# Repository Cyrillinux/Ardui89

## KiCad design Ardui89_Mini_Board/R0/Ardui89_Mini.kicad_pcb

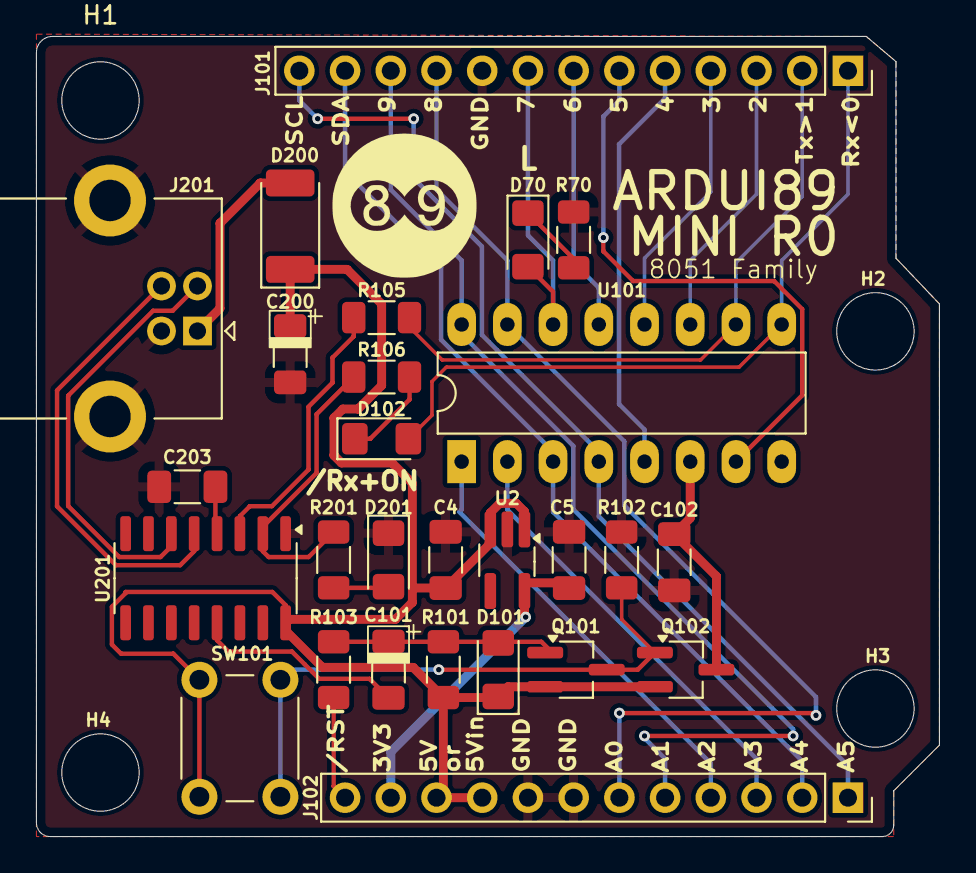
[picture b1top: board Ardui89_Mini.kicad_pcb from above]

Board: 2 copper layers, 50.2 x 44.5 mm, 31 parts (0 on the bottom side), 31 nets.

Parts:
C4, C5, C102, C203: 100n; C_1206_3216Metric_Pad1.33x1.80mm_HandSolder
C101, C200: 10µ; C_1206_POL_3216Metric_Pad1.33x1.80mm_HandSolder
D70: LED BUILTIN; D_1206_3216Metric_Pad1.42x1.75mm_HandSolder
D101, D102: 1N5819W; D_1206_3216Metric_Pad1.42x1.75mm_HandSolder
D200: SM34; D_MELF
D201: /Rx LED + OK; D_1206_3216Metric_Pad1.42x1.75mm_HandSolder
H1, H2, H3: MountingHole; MountingHole_4.3mm_M4_DIN965
H4: Mounting Hole 4.3mm; MountingHole_4.3mm_M4_DIN965
J101: Conn_01x13; PinSocket_1x13_P2.54mm_Vertical
J102: Conn_01x12; PinSocket_1x12_P2.54mm_Vertical
J201: USB_TYPE_B; USB_B_Lumberg_2411_02_Horizontal
Q101, Q102: MMBT2907; TSOT-23_HandSoldering
R70, R101, R103, R201: 1k; R_1206_3216Metric_Pad1.30x1.75mm_HandSolder
R102: 4k7; R_1206_3216Metric_Pad1.30x1.75mm_HandSolder
R105, R106: 330; R_1206_3216Metric_Pad1.30x1.75mm_HandSolder
SW101: SW_Push; SW_PUSH_6mm
U2: LP2985-33DBVR; TSOT-23-5_HandSoldering
U101: DIP-16_W7.62mm_LongPads
U201: CH340C; SOIC-16_3.9x9.9mm_P1.27mm

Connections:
/3.3V: C5.1, J102.11, U2.5 (VOUT)
/A0_D8: J101.10, J102.6, U101.15 ((CCP1/ADC0)_P1.0)
/A1_D9: J101.11, J102.5, U101.16 ((CCP0/ADC1)_P1.1)
/A2: J102.4, U101.1 ((CMP0/ECI/SS/ADC2)_P1.2)
/A3: J102.3, U101.2 ((MOSI/ADC3)_P1.3)
/A4_SDA: J101.12, J102.2, U101.3 ((MISO/ADC4)_P1.4)
/A5_SCL: J101.13, J102.1, U101.4 ((SCLK/ADC5)_P1.5)
/D0: D102.2 (A), J101.1, U101.9 ((RxD/_INT4)_P3.0)
/D1: J101.2, R105.1, U101.10 ((TxD/T2)_P3.1)
/D2: J101.3, U101.11 ((INT0)_P3.2)
/D3: J101.4, U101.12 ((INT1)_P3.3)
/D4: J101.5, U101.5 ((RESET/CMP-/SyCK0)_P5.4)
/D5: J101.6, U101.7 ((CMP+)_P5.5)
/D6: J101.7, U101.13 ((RxD2/_INT2/CCP12)_P3.6)
/D7: D70.2 (A), J101.8, U101.14 ((TxD2/_INT3/CCP22)_P3.7)
/D+: J201.3 (D+), U201.5 (UD+)
/D-: J201.2 (D-), U201.6 (UD-)
/RTS: C101.2, U201.13 (~DTR)
/Rx: R106.2, R201.1, U201.2 (TXD)
/Tx: R105.2, U201.3 (RXD)
//RST: J102.12, R103.2
GND: C4.2, C5.2, C102.2, C200.2, C203.2, D201.1 (K), J101.9, J102.7, J102.8, J201.4 (GND), J201.5 (Shield_1), R70.2, R102.2, U2.2 (GND), U201.1 (GND)
unnamed: D70.1 (K), R70.1
unnamed: C101.1, D101.2 (A), Q101.1 (B), R101.2, R103.1
unnamed: D102.1 (K), R106.1
unnamed: D200.2 (A), J201.1 (Vbus)
unnamed: D201.2 (A), R201.2
unnamed: Q101.3 (C), Q102.1 (B), R102.1, SW101.1
unnamed: C102.1, Q102.3 (C), U101.6 (VCC)
unnamed: C203.1, U201.4 (V3)
VCC: C4.1, C200.1, D101.1 (K), D200.1 (K), J102.9, J102.10, Q101.2 (E), Q102.2 (E), R101.1, SW101.2, U2.1 (VIN), U2.3 (ON/~OFF), U201.16 (VCC)

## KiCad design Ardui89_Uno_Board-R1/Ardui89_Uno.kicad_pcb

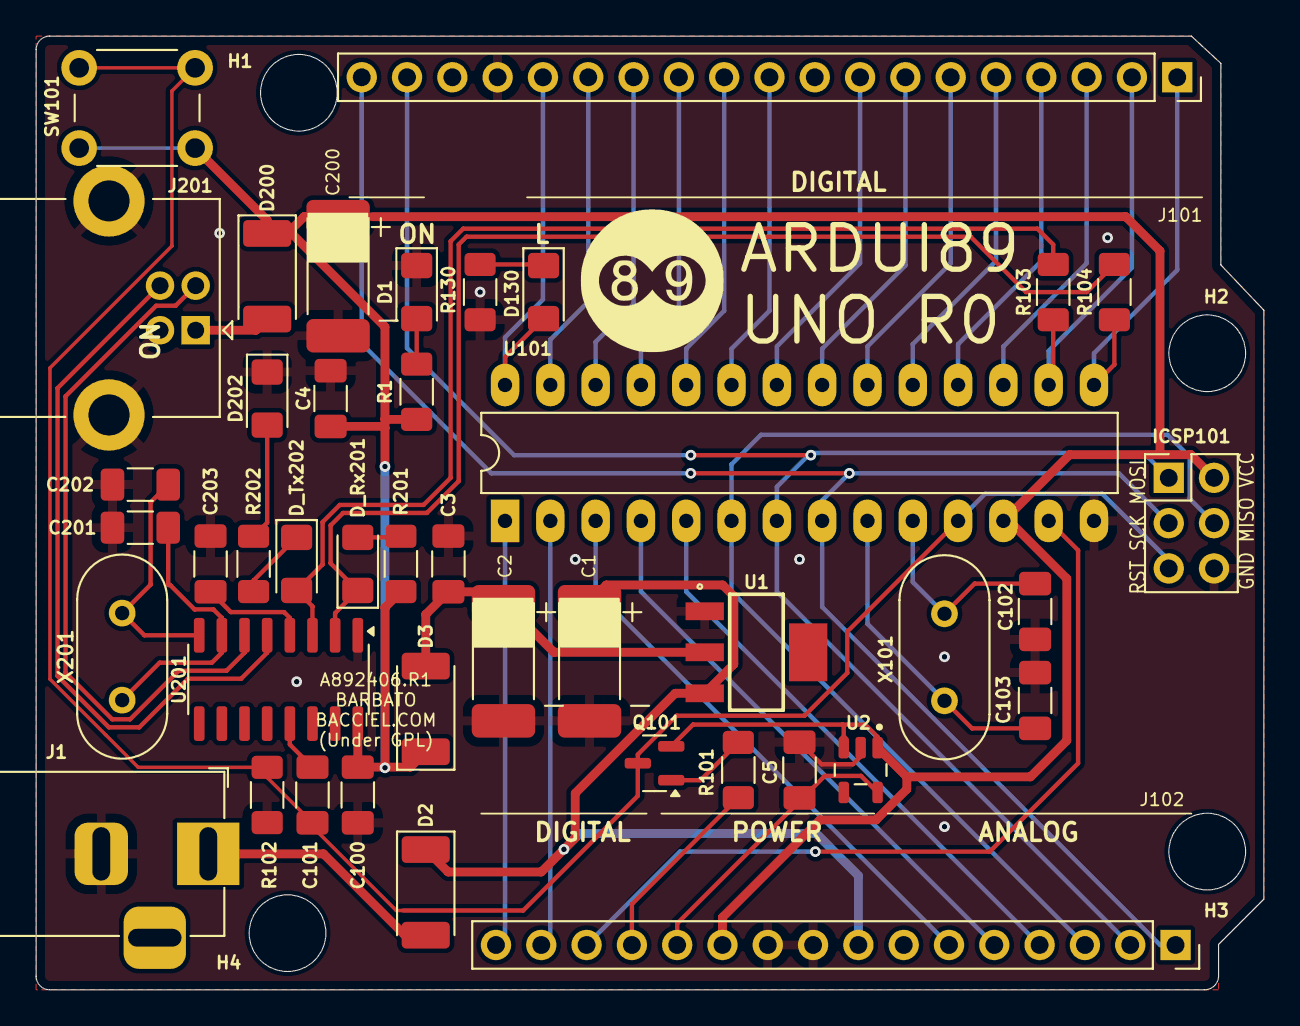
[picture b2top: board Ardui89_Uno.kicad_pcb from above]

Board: 2 copper layers, 68.8 x 53.5 mm, 46 parts (0 on the bottom side), 48 nets.

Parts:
C1: 10uF; C_2512_Pol_Tantale_Trainning
C2: 47uF; C_2512_Pol_Tantale_Trainning
C3, C4, C5, C100, C101, C203: 100n; C_1206_3216Metric_Pad1.33x1.80mm_HandSolder
C102, C103: 22p; C_1206_3216Metric_Pad1.33x1.80mm_HandSolder
C200: 1µ; C_2512_Pol_Tantale_Trainning
C201, C202: 27p; C_1206_3216Metric_Pad1.33x1.80mm_HandSolder
D1: LED; D_1206_3216Metric_Pad1.42x1.75mm_HandSolder
D2, D3, D200: SN4007; D_MELF
D130: LED BUILTIN; D_1206_3216Metric_Pad1.42x1.75mm_HandSolder
D202: 1N4148W; D_1206_3216Metric_Pad1.42x1.75mm_HandSolder
D_Rx201: Rx LED; D_1206_3216Metric_Pad1.42x1.75mm_HandSolder
D_Tx202: Tx LED; D_1206_3216Metric_Pad1.42x1.75mm_HandSolder
H1: Mounting Hole 4.3mm; MountingHole_4.3mm_M4_DIN965
H2, H3, H4: MountingHole; MountingHole_4.3mm_M4_DIN965
ICSP101: M20-9980346; PinHeader_2x03_P2.54mm_Vertical
J1: Jack-DC; BarrelJack_Horizontal
J101: Conn_01x19; Ardu89_Uno_Digital_Connector
J102: Conn_01x16; Ardu89_Uno_Analog_Power_Connector
J201: USB_TYPE_B; USB_B_Lumberg_2411_02_Horizontal
Q101: BC856; SOT-23
R1, R103, R104: 1K; R_1206_3216Metric_Pad1.30x1.75mm_HandSolder
R101, R130, R201, R202: 1k; R_1206_3216Metric_Pad1.30x1.75mm_HandSolder
R102: 10K; R_1206_3216Metric_Pad1.30x1.75mm_HandSolder
SW101: SW_Push; SW_PUSH_6mm
U1: LD1117S50TR; SOT230P700X180-4N
U2: LP2985-33DBVR; SOT95P280X145-5N
U101: STC15F2K16/32-DIP28; DIP-28_W7.62mm_LongPads
U201: CH340G; SOIC-16_3.9x9.9mm_P1.27mm
X101: 11.0592MHz; Crystal_HC49-4H_Vertical
X201: 12MHz; Crystal_HC49-4H_Vertical

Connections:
/3.3V: C5.1, J102.12, U2.5 (VOUT)
/A0: J102.6, U101.3 ((CCP1/ADC0)_P1.0)
/A1: J102.5, U101.4 ((CCP0/ADC1)_P1.1)
/A2: J102.4, U101.5 ((CMP0/ECI/SS/ADC2)_P1.2)
/A3: ICSP101.4, J102.3, U101.6 ((MOSI/ADC3)_P1.3)
/A4_SDA: ICSP101.1, J101.18, J102.2, U101.7 ((MISO/ADC4)_P1.4)
/A5_SCL: ICSP101.3, J101.19, J102.1, U101.8 ((SCLK/ADC5)_P1.5)
/D0: J101.1, R104.1, U101.15 ((RxD/_INT4)_P3.0)
/D1: J101.2, R103.1, U101.16 ((TxD/T2)_P3.1)
/D2: J101.3, U101.17 ((INT0)_P3.2)
/D3: J101.4, U101.18 ((INT1)_P3.3)
/D4: J101.5, U101.19 ((ECI2/T0)_P3.4)
/D5: J101.6, U101.20 ((T0CLK0/CCP02)_P3.5)
/D6: J101.7, U101.21 ((RxD2/_INT2/CCP12)_P3.6)
/D7: J101.8, U101.22 ((TxD2/_INT3/CCP22)_P3.7)
/D8: J101.10, U101.23 ((RSTOUT_LOW)_P2.0)
/D9: J101.11, U101.24 ((SCLK2)_P2.1)
/D10: J101.12, U101.25 ((MISO2)_P2.2)
/D11: J101.13, U101.26 ((MOSI2)_P2.3)
/D12: J101.14, U101.27 ((ECI3/SS2)_P2.4)
/D13: D130.2 (A), J101.15, U101.28 ((CCP03)_P2.5)
/D20: J102.16, U101.1 ((CCP13)_P2.6)
/D21: J102.15, U101.2 ((CCP23)_P2.7)
/D22: J102.14, U101.13 ((CMP+)_P5.5)
/D+: J201.3 (D+), U201.5 (UD+)
/D-: J201.2 (D-), U201.6 (UD-)
/DTR: C101.2, U201.13 (~DTR)
/RESET: C101.1, ICSP101.5, Q101.3 (C), R102.2, SW101.1, U101.11 ((RESET/CMP-/SyCK0)_P5.4)
/Rx: D_Rx201.1 (K), R104.2, U201.2 (TXD)
/Tx: D_Tx202.2 (A), R103.2, U201.3 (RXD)
/Vin: C1.1, D2.1 (K), J102.8, U1.3 (Vin)
//RST: J102.13, R101.2
GND: C1.2, C2.2, C3.2, C4.2, C5.2, C100.2, C102.2, C103.2, C200.2, C201.2, C202.2, C203.2, D1.1 (K), D202.1 (K), ICSP101.6, J1.2, J101.16, J102.9, J102.10, J201.4 (GND), J201.5 (Shield_1), R102.1, R130.2, U1.1 (GND), U2.2 (GND), U101.14 (GND), U201.1 (GND)
unnamed: D1.2 (A), R1.2
unnamed: D2.2 (A), J1.1
unnamed: C2.1, C3.1, D3.2 (A), U1.2 (Vout)
unnamed: D130.1 (K), R130.1
unnamed: D200.2 (A), J201.1 (Vbus)
unnamed: D202.2 (A), R202.1
unnamed: D_Rx201.2 (A), R201.2
unnamed: D_Tx202.1 (K), R202.2
unnamed: Q101.1 (B), R101.1
unnamed: C102.1, U101.10 ((XT1/TxD3/ADC7)_P1.7), X101.1
unnamed: C103.1, U101.9 ((XT2/RxD3/ADC6)_P1.6), X101.2
unnamed: C203.1, U201.4 (V3)
unnamed: C201.1, U201.7 (XI), X201.2
unnamed: C202.1, U201.8 (XO), X201.1
VCC: C4.1, C100.1, C200.1, D3.1 (K), D200.1 (K), ICSP101.2, J102.11, Q101.2 (E), R1.1, R201.1, SW101.2, U2.1 (VIN), U2.3 (ON/~OFF), U101.12 (VCC), U201.16 (VCC)

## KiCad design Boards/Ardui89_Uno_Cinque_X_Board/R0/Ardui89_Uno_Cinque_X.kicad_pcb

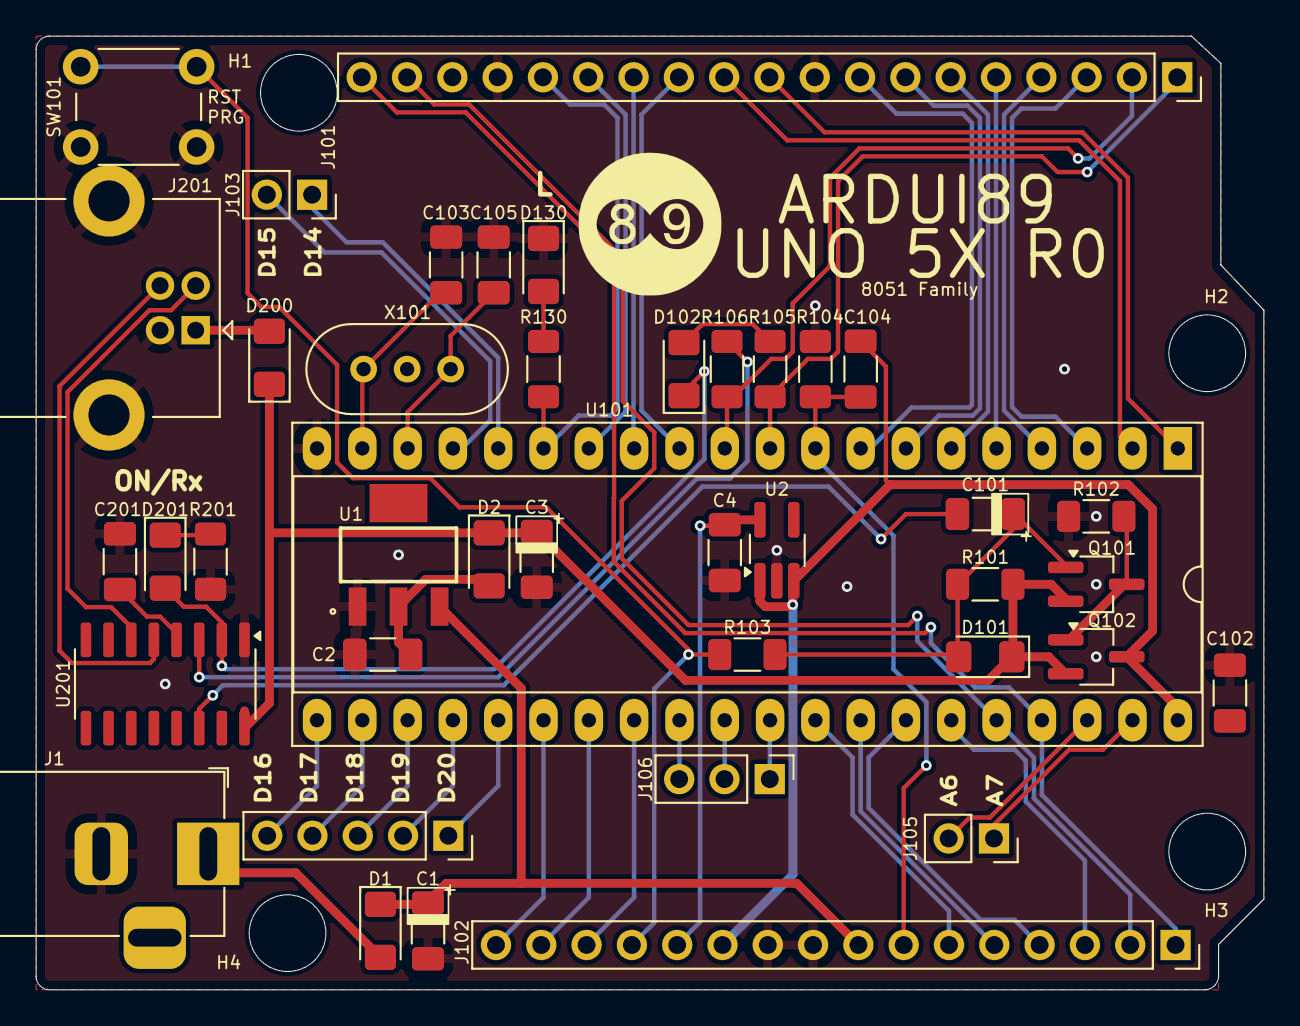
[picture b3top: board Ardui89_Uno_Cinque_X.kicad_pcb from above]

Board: 2 copper layers, 68.8 x 53.5 mm, 45 parts (0 on the bottom side), 58 nets.

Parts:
C1, C3, C101: 10µ; C_1206_POL_3216Metric_Pad1.33x1.80mm_HandSolder
C2, C4, C102, C104, C201: 100n; C_1206_3216Metric_Pad1.33x1.80mm_HandSolder
C103, C105: 22p; C_1206_3216Metric_Pad1.33x1.80mm_HandSolder
D1, D2, D200: SM34; D_1206_3216Metric_Pad1.42x1.75mm_HandSolder
D101, D102: 1N5819W; D_1206_3216Metric_Pad1.42x1.75mm_HandSolder
D130: BUILTIN_LED; D_1206_3216Metric_Pad1.42x1.75mm_HandSolder
D201: ON+Rx LED; D_1206_3216Metric_Pad1.42x1.75mm_HandSolder
H1: Mounting Hole 4.3mm; MountingHole_4.3mm_M4_DIN965
H2, H3, H4: MountingHole; MountingHole_4.3mm_M4_DIN965
J1: Jack-DC; BarrelJack_Horizontal
J101: Conn_01x19; Ardu89_Uno_Digital_Connector
J102: Conn_01x16; Ardu89_Uno_Analog_Power_Connector
J103, J105: Extented Port; PinSocket_1x02_P2.54mm_Vertical
J104: Extended Port; PinSocket_1x05_P2.54mm_Vertical
J106: Conn_01x03; PinHeader_1x03_P2.54mm_Vertical
J201: USB_TYPE_B; USB_B_Lumberg_2411_02_Horizontal
Q101, Q102: MMBTA2907; TSOT-23_HandSoldering
R101, R103, R104, R130, R201: 1k; R_1206_3216Metric_Pad1.30x1.75mm_HandSolder
R102: 4k7; R_1206_3216Metric_Pad1.30x1.75mm_HandSolder
R105, R106: 330; R_1206_3216Metric_Pad1.30x1.75mm_HandSolder
SW101: SW_Push; SW_PUSH_6mm
U1: LD1117S50TR; SOT230P700X180-4N
U2: LP2985-33DBVR; TSOT-23-5_HandSoldering
U101: 89C5x; DIP-40_W15.24mm_Socket_LongPads
U201: CH340C; SOIC-16_3.9x9.9mm_P1.27mm
X101: 11.0592MHz; Crystal_HC49-U-3PinB_Vertical

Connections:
/3.3V: C4.1, J102.12, U2.5 (VOUT)
/A0: J102.6, U101.32 (P0.7_(AD7))
/A1: J102.5, U101.33 (P0.6_(AD6))
/A2: J102.4, U101.34 (P0.5_(AD5))
/A3: J102.3, U101.35 (P0.4_(AD4))
/A4_SDA: J101.18, J102.2, U101.36 (P0.3_(AD3))
/A5_SCL: J101.19, J102.1, U101.37 (P0.2_(AD2))
/A6: J105.2, U101.38 (P0.1_(AD1))
/A7: J105.1, U101.39 (P0.0_(AD0))
/D0: J101.1, R105.1, U101.10 ((RXD)_P3.0)
/D1: J101.2, R106.1, U101.11 ((TXD)_P3.1)
/D2: J101.3, U101.3 (P1.2)
/D3: J101.4, U101.4 (P1.3)
/D4: J101.5, U101.5 (P1.4)
/D5: J101.6, U101.6 ((MOSI)_P1.5)
/D6: J101.7, U101.7 ((MISO)_P1.6)
/D7: J101.8, U101.8 ((SCK)_P1.7)
/D8: J101.10, U101.1 ((T2)_P1.0)
/D9: J101.11, U101.2 ((T2_EX)_P1.1)
/D10: J101.12, U101.12 ((INT0)_P3.2)
/D11: J101.13, U101.13 ((INT1)_P3.3)
/D12: J101.14, U101.14 ((T0)_P3.4)
/D13: J101.15, R130.2, U101.15 ((T1)_P3.5)
/D14: J103.1, U101.16 ((WR)_P3.6)
/D15: J103.2, U101.17 ((RD)_P3.7)
/D16: J104.5, U101.21 (P2.0_(A8))
/D17: J104.4, U101.22 (P2.1_(A9))
/D18: J104.3, U101.23 (P2.2_(A10))
/D19: J104.2, U101.24 (P2.3_(A11))
/D20: J104.1, U101.25 (P2.4_(A12))
/D21: J102.16, U101.26 (P2.5_(A13))
/D22: J102.15, U101.27 (P2.6_(A14))
/D23: J102.14, U101.28 (P2.7_(A15))
/D+: J201.3 (D+), U201.5 (UD+)
/D-: J201.2 (D-), U201.6 (UD-)
/RESET: C104.2, J102.7, R104.2, U101.9 (RST)
/RTS: C101.2, U201.14 (~RTS)
/Rx: D102.1 (K), D201.2 (A), U201.2 (TXD)
/Tx: R106.2, U201.3 (RXD)
/Vin: C1.1, D1.1 (K), J102.8, U1.3 (Vin)
//RST: J102.13, R103.1, SW101.2
GND: C1.2, C2.2, C3.2, C4.2, C102.2, C103.2, C105.2, C201.2, D130.1 (K), J1.2, J101.9, J101.16, J102.9, J102.10, J201.4 (GND), J201.5 (Shield_1), R102.2, R104.1, R201.1, SW101.1, U1.1 (GND), U2.2 (GND), U101.20 (GND), U201.1 (GND)
unnamed: D1.2 (A), J1.1
unnamed: C2.1, D2.2 (A), U1.2 (Vout)
unnamed: C101.1, D101.2 (A), Q101.1 (B), R101.2, R103.2
unnamed: D102.2 (A), R105.2
unnamed: D130.2 (A), R130.1
unnamed: D200.2 (A), J201.1 (Vbus)
unnamed: D201.1 (K), R201.2
unnamed: J106.1, U101.31 (~EA/VPP)
unnamed: J106.2, U101.30 (ALE/~PROG)
unnamed: J106.3, U101.29 (~PSEN)
unnamed: Q101.3 (C), Q102.1 (B), R102.1
unnamed: C103.1, U101.19 (XTAL1), X101.2
unnamed: C105.1, U101.18 (XTAL2), X101.1
unnamed: C201.1, U201.4 (V3)
VCC: C3.1, D2.1 (K), D101.1 (K), D200.1 (K), Q101.2 (E), Q102.2 (E), R101.1, U201.16 (VCC)
VCPU: C102.1, C104.1, J102.11, Q102.3 (C), U2.1 (VIN), U2.3 (ON/~OFF), U101.40 (VCC)

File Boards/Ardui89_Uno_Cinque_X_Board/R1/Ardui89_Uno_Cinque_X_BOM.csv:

"Reference","Value","Footprint","Qty","#","Description"
"C1,C3,C101","10µ","PRJLIB:C_1206_POL_3216Metric_Pad1.33x1.80mm_HandSolder","3","1","C_1206_POL_3216Metric_Pad1.33x1.80mm/A/10µF/10V/Tantalum"
"C2,C4,C102,C104,C201","100n","Capacitor_SMD:C_1206_3216Metric_Pad1.33x1.80mm_HandSolder","5","2","C_1206_3216Metric_Pad1.33x1.80mm/Ceramic"
"C103,C105","22p","Capacitor_SMD:C_1206_3216Metric_Pad1.33x1.80mm_HandSolder","2","3","C_1206_3216Metric_Pad1.33x1.80mm/Ceramic"
"D1,D2,D101,D200","1N5819W","Diode_SMD:D_1206_3216Metric_Pad1.42x1.75mm_HandSolder","4","4","D_1206_3216Metric_Pad1.42x1.75mm"
"D130","BUILTIN_LED/Blue","Diode_SMD:D_1206_3216Metric_Pad1.42x1.75mm_HandSolder","1","5","D_1206_3216Metric_Pad1.42x1.75mm_HandSolder/Blue"
"D201","ON+Rx LED/Orange","Diode_SMD:D_1206_3216Metric_Pad1.42x1.75mm_HandSolder","1","6","D_1206_3216Metric_Pad1.42x1.75mm_HandSolder/Orange"
"J1","BarrelJack_Horizontal_5.5mmx2.1mm","Connector_BarrelJack:BarrelJack_Horizontal","1","7","DC Barrel Jack"
"J101","PinSocket_1x19_P2.54mm_Vertical","BACKCIEL:Ardu89_Uno_Digital_Connector","1","8","Generic connector, single row, 01x19, script generated (kicad-library-utils/schlib/autogen/connector/)"
"J102","PinSocket_1x16_P2.54mm_Vertical","BACKCIEL:Ardu89_Uno_Analog_Power_Connector","1","9","Generic connector, single row, 01x16, script generated (kicad-library-utils/schlib/autogen/connector/)"
"J103,J105","PinSocket_1x02_P2.54mm_Vertical","Connector_PinSocket_2.54mm:PinSocket_1x02_P2.54mm_Vertical","2","10","Generic connector, single row, 01x02, script generated (kicad-library-utils/schlib/autogen/connector/)"
"J104","PinSocket_1x05_P2.54mm_Vertical","Connector_PinSocket_2.54mm:PinSocket_1x05_P2.54mm_Vertical","1","11","Generic connector, single row, 01x05, script generated (kicad-library-utils/schlib/autogen/connector/)"
"J106","PinHeader_1x03_P2.54mm_Vertical","Connector_PinHeader_2.54mm:PinHeader_1x03_P2.54mm_Vertical","1","12","Generic connector, single row, 01x03, script generated (kicad-library-utils/schlib/autogen/connector/)"
"J200","USB_B_Lumberg_2411_02_Horizontal","Connector_USB:USB_B_Lumberg_2411_02_Horizontal","1","13","USB Type-B Connector"
"Q101","SI2301","Package_TO_SOT_SMD:TSOT-23_HandSoldering","1","14","SI2301"
"Q102","MMBTA2907","Package_TO_SOT_SMD:TSOT-23_HandSoldering","1","15","MMBTA2907"
"R101","20k","Resistor_SMD:R_1206_3216Metric_Pad1.30x1.75mm_HandSolder","1","16","R_1206_3216Metric_Pad1.30x1.75mm"
"R102,R104,R130","1k","Resistor_SMD:R_1206_3216Metric_Pad1.30x1.75mm_HandSolder","3","17","R_1206_3216Metric_Pad1.30x1.75mm"
"R103","4k7","Resistor_SMD:R_1206_3216Metric_Pad1.30x1.75mm_HandSolder","1","18","R_1206_3216Metric_Pad1.30x1.75mm"
"R105,R106","330","Resistor_SMD:R_1206_3216Metric_Pad1.30x1.75mm_HandSolder","2","19","R_1206_3216Metric_Pad1.30x1.75mm"
"R201","2k2","Resistor_SMD:R_1206_3216Metric_Pad1.30x1.75mm_HandSolder","1","20","R_1206_3216Metric_Pad1.30x1.75mm"
"SW101","SW_Push_6mmx6mmx5mm","Button_Switch_THT:SW_PUSH_6mm","1","21","Push button switch, generic, 4 pins"
"U1","LD1117S50TR","PRJ:SOT230P700X180-4N","1","22","5V Fixed LDO"
"U2","LP2985-33DBVR","Package_TO_SOT_SMD:TSOT-23-5_HandSoldering","1","23","3V3 Fixed LDO Regulator"
"U101","89C5x","Package_DIP:DIP-40_W15.24mm_Socket_LongPads","1","24","Tulip Socket DIP-40 / Not 80C5x directly mounted"
"U201","CH340C","Package_SO:SOIC-16_3.9x9.9mm_P1.27mm","1","25","Package_SO:SOIC-16_3.9x9.9mm_P1.27mm"
"X101",">=11.0592MHz","PRJLIB:Crystal_HC49-U-3PinB_Vertical_Socket","1","26","Tulip Socket 2.54 01x03 SIL"

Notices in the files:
Ardui89_Mini_Board/R0/Ardui89_Mini.kicad_pcb:
(Under GPL)
